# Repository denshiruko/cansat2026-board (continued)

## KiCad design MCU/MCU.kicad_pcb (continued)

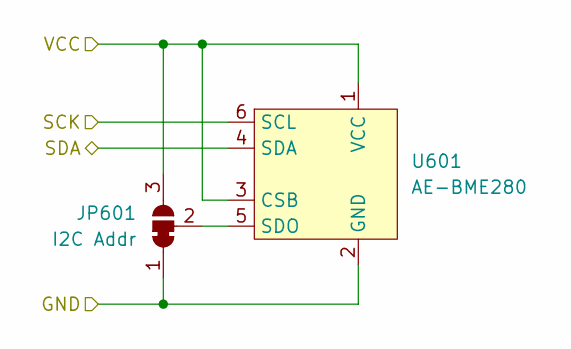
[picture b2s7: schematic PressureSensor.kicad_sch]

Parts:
JP601: I2C Addr; SolderJumper-3_P1.3mm_Bridged12_RoundedPad1.0x1.5mm_NumberL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
U601: AE-BME280

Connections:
/I2C1SCL: U601.6 (SCL); also elsewhere on the board
/I2C1SDA: U601.4 (SDA); also elsewhere on the board
/VCC: JP601.3 (B), U601.1 (VCC), U601.3 (CSB); also elsewhere on the board
GND: JP601.1 (A), U601.2 (GND); also elsewhere on the board
unnamed: JP601.2 (C), U601.5 (SDO)

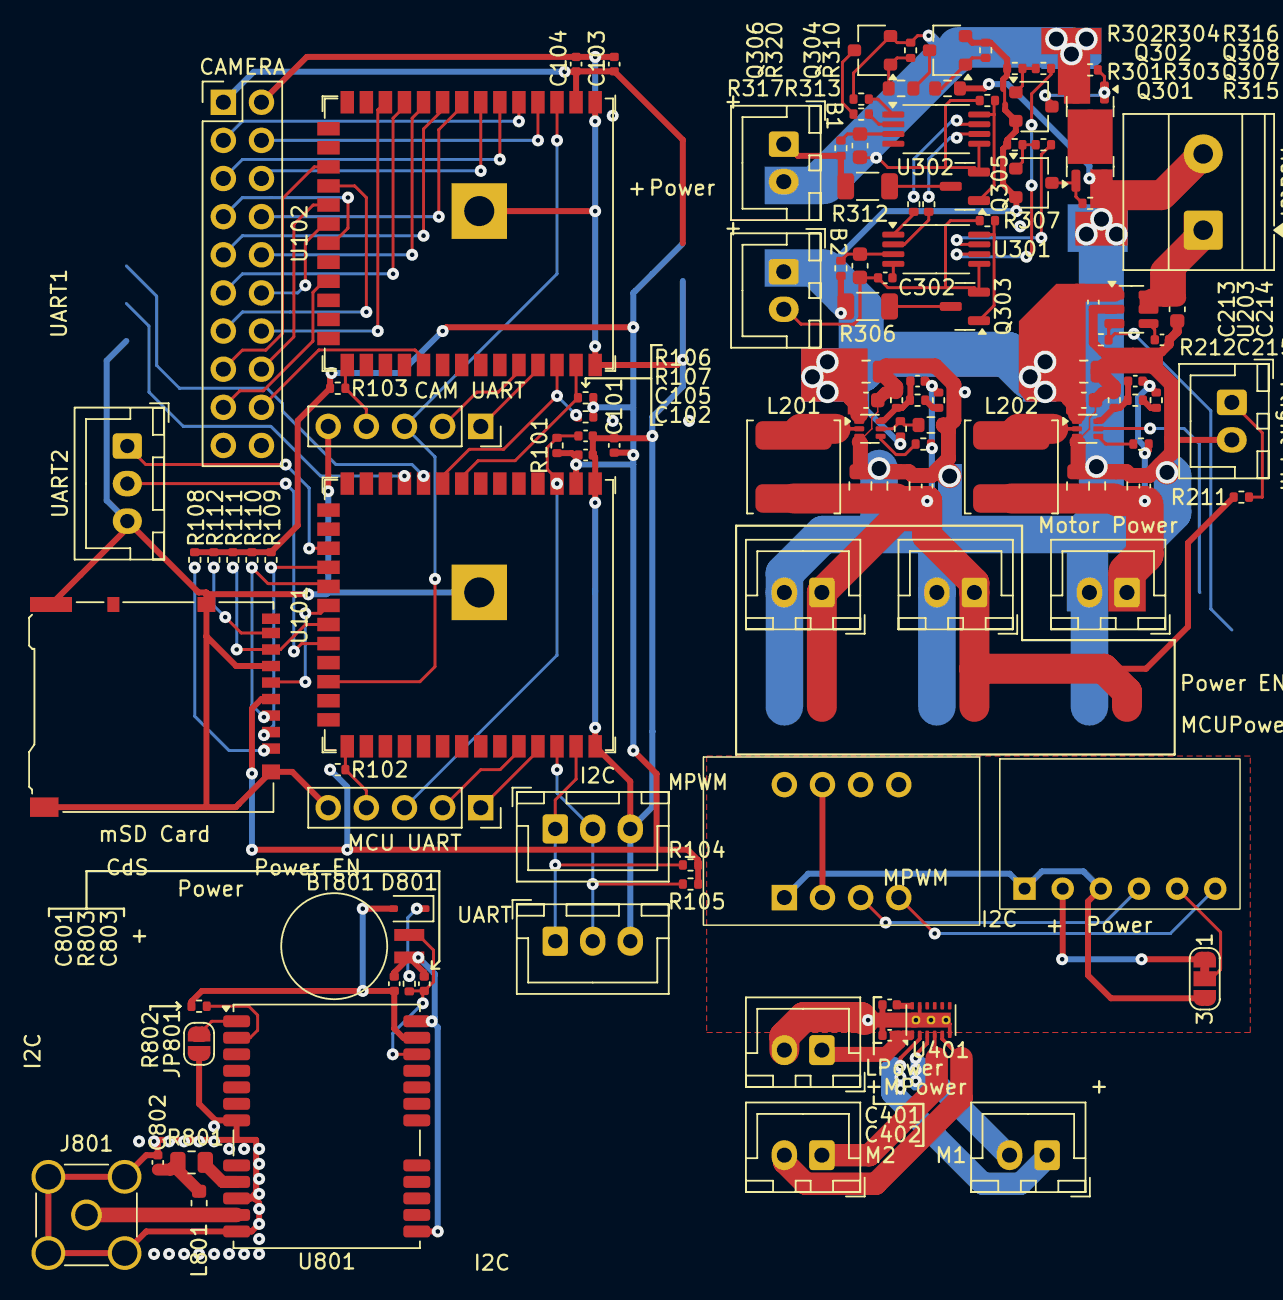
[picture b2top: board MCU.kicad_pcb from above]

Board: 2 copper layers, 119 parts (0 on the bottom side), 99 nets.

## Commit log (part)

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2026-04-03 Import: from cansat2025-board
    cansat2025-boardのv1.0からそのままコピーしてきた。
    これから修正とかしていく
2026-04-03 Version Update: 9.0->10.0
2026-04-03 Update: コネクタをだいぶ消した
    手配線になるね
2026-04-03 Update: 隙間を詰めてみた
    でも大きいなあ
    裏面が結構空いてる
2026-04-03 Rename: MCU/ -> cansat2026/
2026-04-03 Update: MCUシートを作成
    MCU部分を分けた
    あとでFPGAつけるかもしれないしね
2026-04-03 Update: ラベルをワイヤーにした
    ラベルが衝突してERCが出たから
2026-04-23 Update: いろいろした
    無線変えた
    カメラのコネクタ変えた
    i2cセンサ変えた
    電源変えた:1.2V,3.8V,3.3V
    IOエキスパンダ追加
    FPGA追加
2026-04-27 Update: MDと電源とか
    MD変えた
    モーター電源と主電源
2026-04-28 Update: いろいろした
    GPS変えた
    USB追加した
    気圧センサ変えた
    FPGA変えた
    MDにキャパシタ追加した
2026-06-28 Update: 完成した
